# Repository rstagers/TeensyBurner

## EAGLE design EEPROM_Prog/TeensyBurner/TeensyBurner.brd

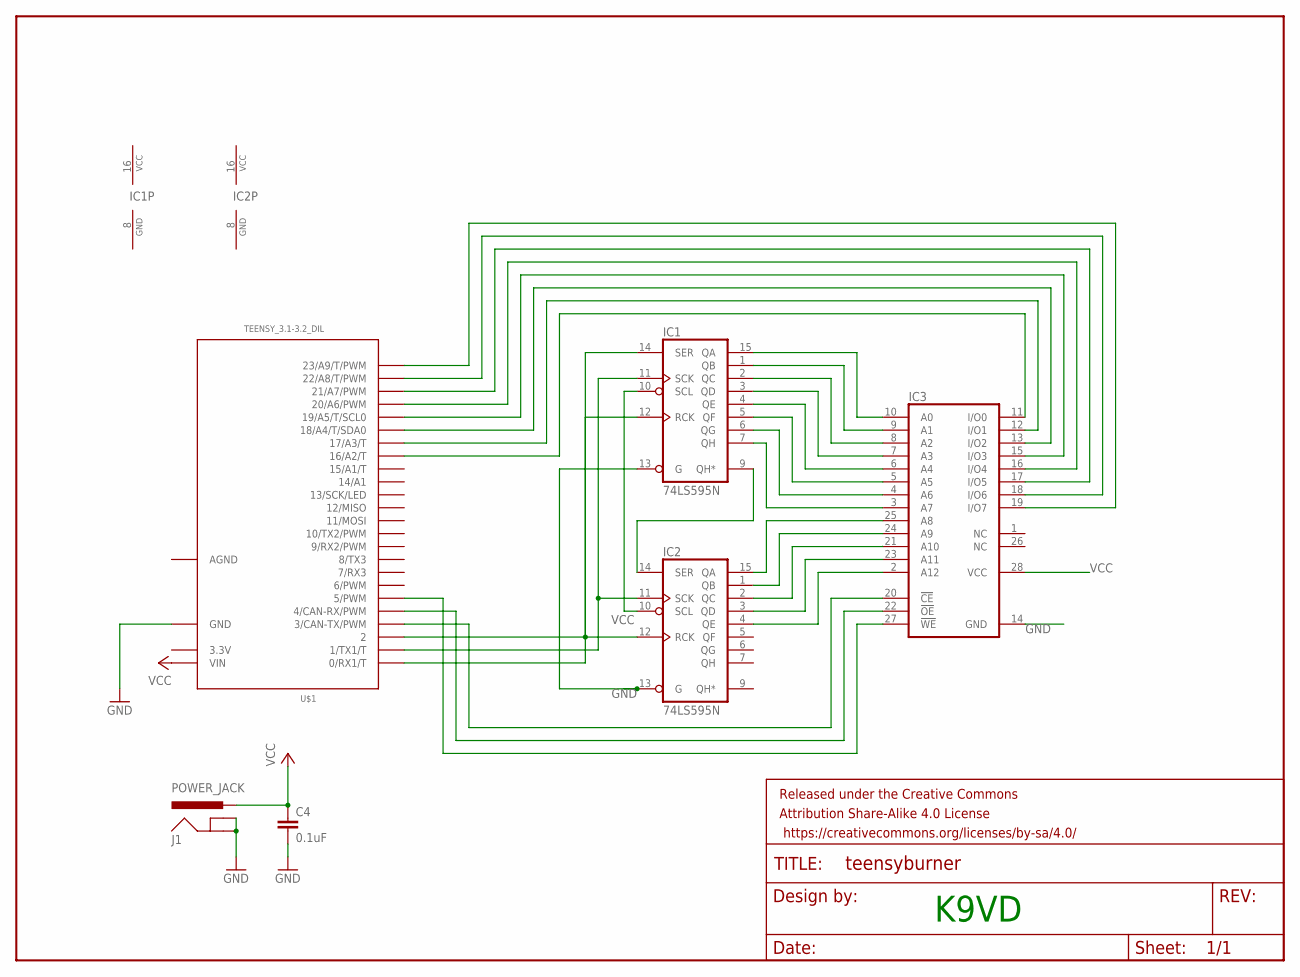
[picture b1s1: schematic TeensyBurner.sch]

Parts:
C4: 0.1uF; CAP-PTH-SMALL-KIT
FRAME1: FRAME-LETTERNO_PACKAGE; DUMMY
IC1, IC2: 74LS595N; DIL16
IC3: 28C64C; DIL28-6
J1: POWER_JACK; POWER_JACK_PTH
U$1: TEENSY_3.1-3.2_DIL; TEENSY_3.0-3.2&LC_DIL

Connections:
3.3V: U$1.3.3V
AGND: U$1.AGND
GND: C4.2, IC1.8 (GND), IC1.13 (G), IC2.8 (GND), IC2.13 (G), IC3.14 (GND), J1.GND, J1.GNDBREAK, U$1.GND
unnamed: IC1.9 (QH*), IC2.14 (SER)
unnamed: IC1.14 (SER), U$1.0 (0/RX1/T)
unnamed: IC1.12 (RCK), IC2.12 (RCK), U$1.2
unnamed: IC1.11 (SCK), IC2.11 (SCK), U$1.1 (1/TX1/T)
unnamed: IC1.15 (QA), IC3.10 (A0)
unnamed: IC1.1 (QB), IC3.9 (A1)
unnamed: IC1.2 (QC), IC3.8 (A2)
unnamed: IC1.3 (QD), IC3.7 (A3)
unnamed: IC1.4 (QE), IC3.6 (A4)
unnamed: IC1.5 (QF), IC3.5 (A5)
unnamed: IC1.6 (QG), IC3.4 (A6)
unnamed: IC1.7 (QH), IC3.3 (A7)
unnamed: IC2.15 (QA), IC3.25 (A8)
unnamed: IC2.1 (QB), IC3.24 (A9)
unnamed: IC2.2 (QC), IC3.21 (A10)
unnamed: IC2.3 (QD), IC3.23 (A11)
unnamed: IC2.4 (QE), IC3.2 (A12)
unnamed: IC3.11 (I/O0), U$1.16/A2 (16/A2/T)
unnamed: IC3.12 (I/O1), U$1.17/A3 (17/A3/T)
unnamed: IC3.13 (I/O2), U$1.18/A4 (18/A4/T/SDA0)
unnamed: IC3.15 (I/O3), U$1.19/A5 (19/A5/T/SCL0)
unnamed: IC3.16 (I/O4), U$1.20/A6 (20/A6/PWM)
unnamed: IC3.17 (I/O5), U$1.21/A7 (21/A7/PWM)
unnamed: IC3.18 (I/O6), U$1.22/A8 (22/A8/T/PWM)
unnamed: IC3.20 (!CE), U$1.3 (3/CAN-TX/PWM)
unnamed: IC3.22 (!OE), U$1.4 (4/CAN-RX/PWM)
unnamed: IC3.27 (!WE), U$1.5 (5/PWM)
unnamed: IC3.19 (I/O7), U$1.23/A9 (23/A9/T/PWM)
VCC: C4.1, IC1.10 (SCL), IC1.16 (VCC), IC2.10 (SCL), IC2.16 (VCC), IC3.28 (VCC), J1.PWR, U$1.VIN

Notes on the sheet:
K9VD

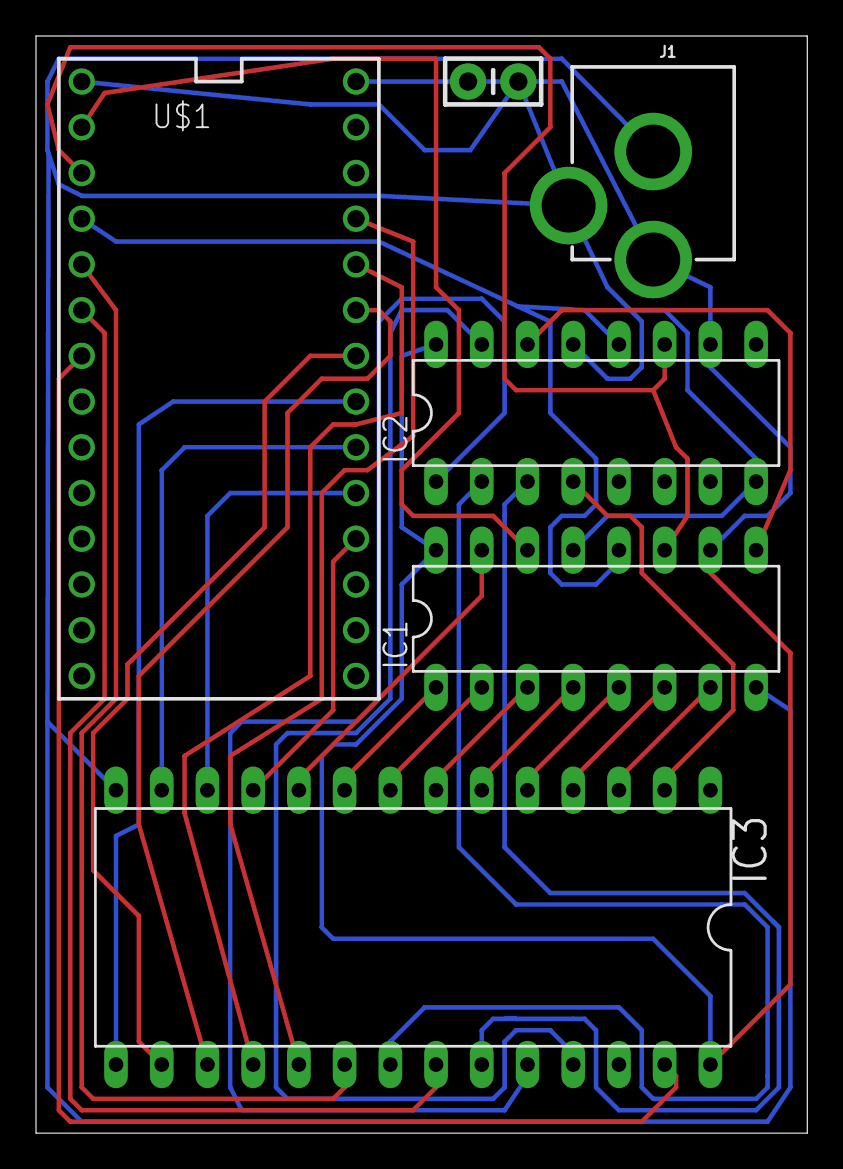
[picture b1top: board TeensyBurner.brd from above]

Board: 2 copper layers, 42.9 x 61.0 mm, 7 parts (0 on the bottom side), 30 nets.

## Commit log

2017-03-16 :boom::camel: Added .gitattributes & .gitignore files
2017-03-16 EEPROM Programmer
    Using the Teensy 3.1 to program 28C16 and 28C64 EEPROMS. Currently the
    schematics are for a 28C64 (VCC, A12 and WE are different). I built a
    new breadboard for the 28C16. The control and address lines on the
    Teensy are the same but the wiring will need to be modified for the chip
    you are using. I only plan on using a breadboard...
2017-03-16 Updated Eagle files
    Upladed an old version, this corrected that.
2017-03-16 Add photo of latest breadboard creation...

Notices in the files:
parts and their libraries:
SparkFun-Capacitors: Licensing: Creative Commons ShareAlike 4.0 International - https://creativecommons.org/licenses/by-sa/4.0
SparkFun-Aesthetics: Released under the Creative Commons Attribution Share-Alike 4.0 License
SparkFun-Aesthetics: https://creativecommons.org/licenses/by-sa/4.0
